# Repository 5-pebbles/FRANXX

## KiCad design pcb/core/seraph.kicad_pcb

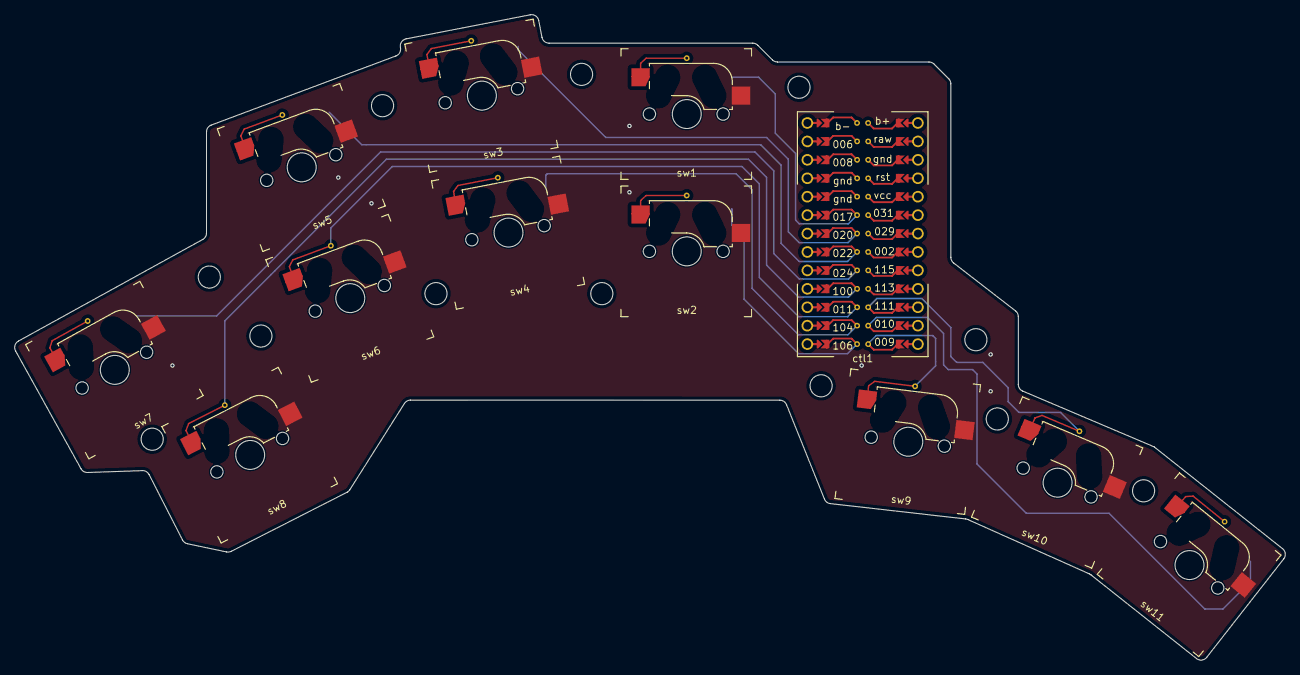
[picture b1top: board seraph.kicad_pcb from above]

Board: 2 copper layers, 175.1 x 89.0 mm, 12 parts (0 on the bottom side), 12 nets.

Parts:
ctl1: Nice!Nano
sw1, sw2, sw3, sw4, sw5, sw6, sw7, sw8, sw9, sw10, sw11: MXHotSwapSwitch

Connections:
gnd: sw1.2, sw2.2, sw3.2, sw4.2, sw5.2, sw6.2, sw7.2, sw8.2, sw9.2, sw10.2, sw11.2
sw1: ctl1.031, sw1.1
sw2: ctl1.009, sw2.1
sw3: ctl1.029, sw3.1
sw4: ctl1.010, sw4.1
sw5: ctl1.002, sw5.1
sw6: ctl1.111, sw6.1
sw7: ctl1.115, sw7.1
sw8: ctl1.113, sw8.1
sw9: ctl1.106, sw9.1
sw10: ctl1.011, sw10.1
sw11: ctl1.104, sw11.1

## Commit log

2025-08-16 init
2025-10-01 refactor(name): rename project from darling to seraph;
2026-01-18 refactor(zmk_module): change zmk module name;
